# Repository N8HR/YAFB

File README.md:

# Yet Another Foxbox (YAFB)
YAFB is an amateur radio fox transmitter designed for an ESP32-S2-Saola-1 and a NiceRF SA818.

Still being worked on and is not in a functional state but there is a cool logo to look at!

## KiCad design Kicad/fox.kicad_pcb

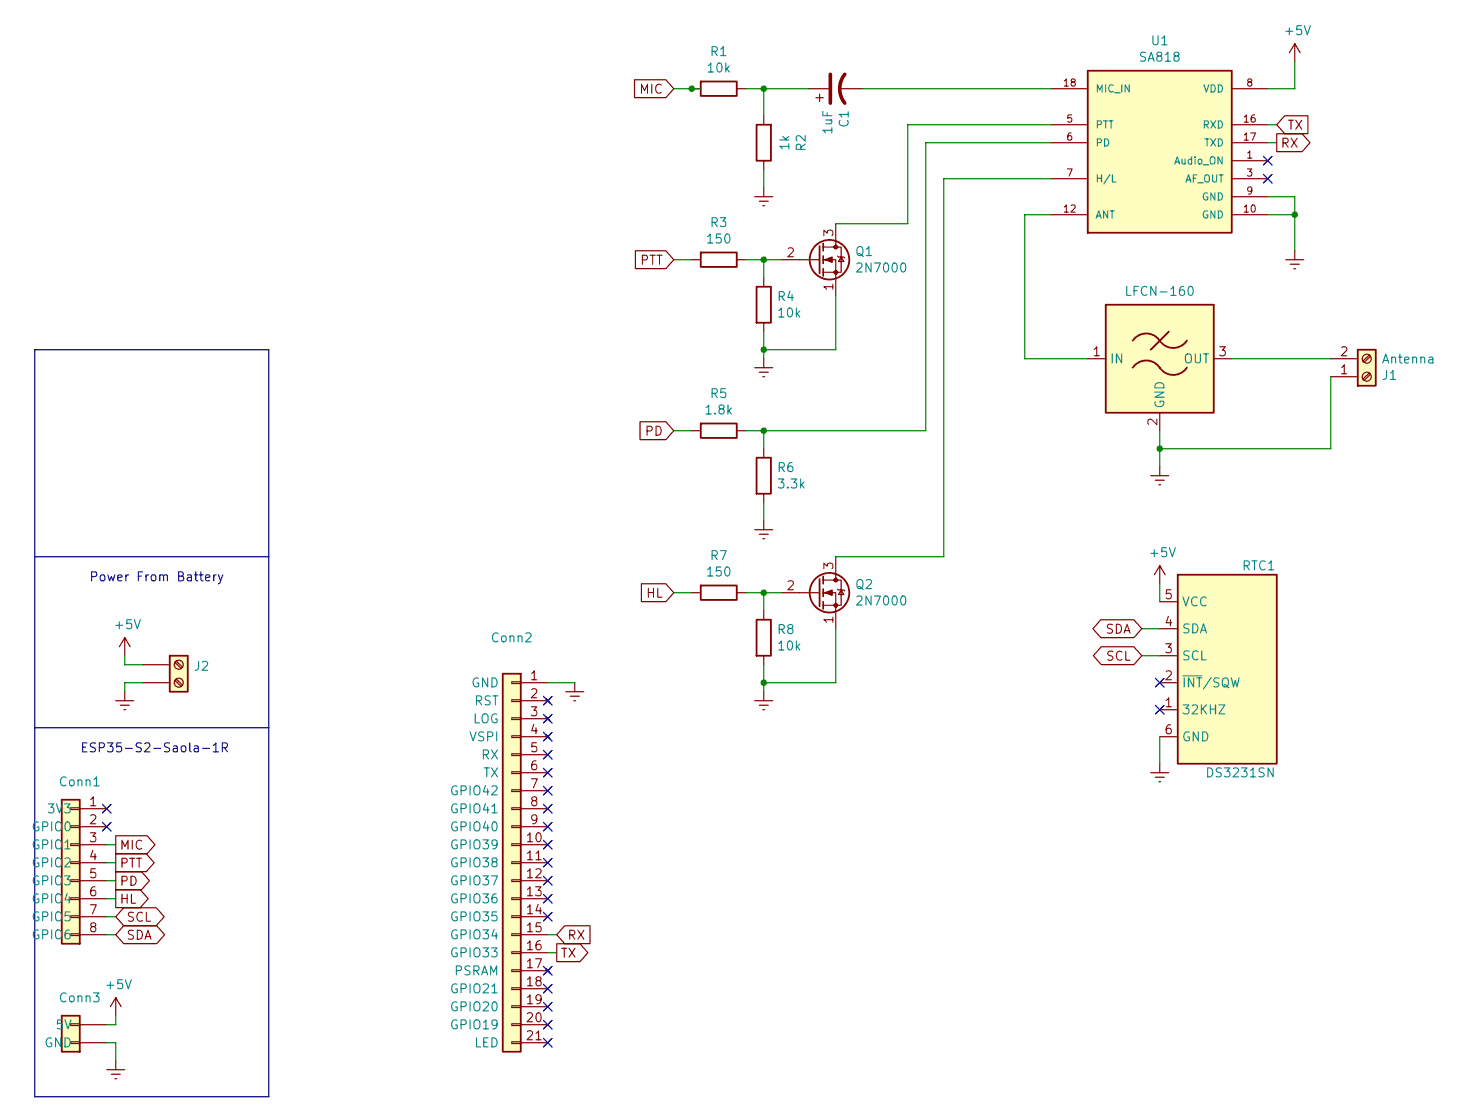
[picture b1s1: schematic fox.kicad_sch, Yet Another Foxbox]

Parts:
C1: 1uF; CP_Radial_D5.0mm_P2.50mm
Conn1: ESP32-S2-Saola-1R_GPIO_1; PinSocket_1x08_P2.54mm_Vertical
Conn2: ESP32-S2-Saola-1R_GPIO_2; PinSocket_1x21_P2.54mm_Vertical
Conn3: ESP32-S2-Saola-1R_Power; PinSocket_1x02_P2.54mm_Vertical
FL1: LFCN-160; Filter_Mini-Circuits_FV1206
J1: Antenna; OSTTA020161
J2: Power; OSTTA020161
Q1, Q2: 2N7000; TO-92_Inline_Wide
R1, R4, R8: 10k; R_Axial_DIN0207_L6.3mm_D2.5mm_P7.62mm_Horizontal
R2: 1k; R_Axial_DIN0207_L6.3mm_D2.5mm_P7.62mm_Horizontal
R3, R7: 150; R_Axial_DIN0207_L6.3mm_D2.5mm_P7.62mm_Horizontal
R5: 1.8k; R_Axial_DIN0207_L6.3mm_D2.5mm_P7.62mm_Horizontal
R6: 3.3k; R_Axial_DIN0207_L6.3mm_D2.5mm_P7.62mm_Horizontal
RTC1: DS3231SN
U1: SA818; DRA818; PART_REV 1.23

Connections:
+5V: Conn3.5v0 (5V), J2.1, RTC1.5 (VCC), U1.8 (VDD)
GNDREF: Conn2.1 (GND), Conn3.GND, FL1.2 (GND), FL1.4 (GND), J1.1, J2.2, Q1.1 (S), Q2.1 (S), R2.1, R4.2, R6.2, R8.2, RTC1.6 (GND), U1.9 (GND), U1.10 (GND)
HL: Conn1.6 (GPIO4), R7.2
MIC: Conn1.3 (GPIO1), R1.2
unnamed: C1.1, R1.1, R2.2
unnamed: C1.2, U1.18 (MIC_IN)
unnamed: FL1.1 (IN), U1.12 (ANT)
unnamed: FL1.3 (OUT), J1.2
unnamed: Q1.2 (G), R3.1, R4.1
unnamed: Q1.3 (D), U1.5 (PTT)
unnamed: Q2.2 (G), R7.1, R8.1
unnamed: Q2.3 (D), U1.7 (H/L)
unnamed: R5.1, R6.1, U1.6 (PD)
PD: Conn1.5 (GPIO3), R5.2
PTT: Conn1.4 (GPIO2), R3.2
RX: Conn2.15 (GPIO34), U1.17 (TXD)
SCL: Conn1.7 (GPIO5), RTC1.3 (SCL)
SDA: Conn1.8 (GPIO6), RTC1.4 (SDA)
TX: Conn2.16 (GPIO33), U1.16 (RXD)

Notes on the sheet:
ESP35-S2-Saola-1R
Power From Battery

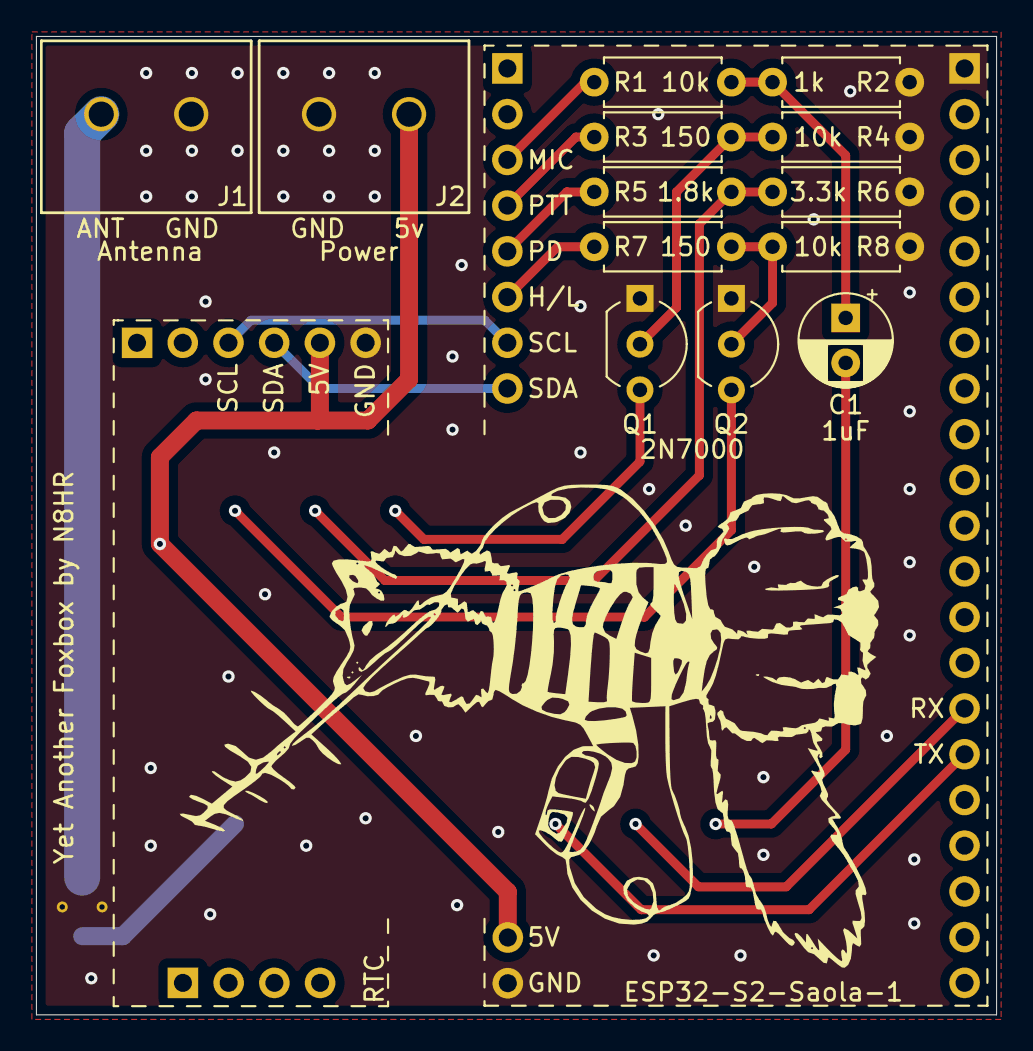
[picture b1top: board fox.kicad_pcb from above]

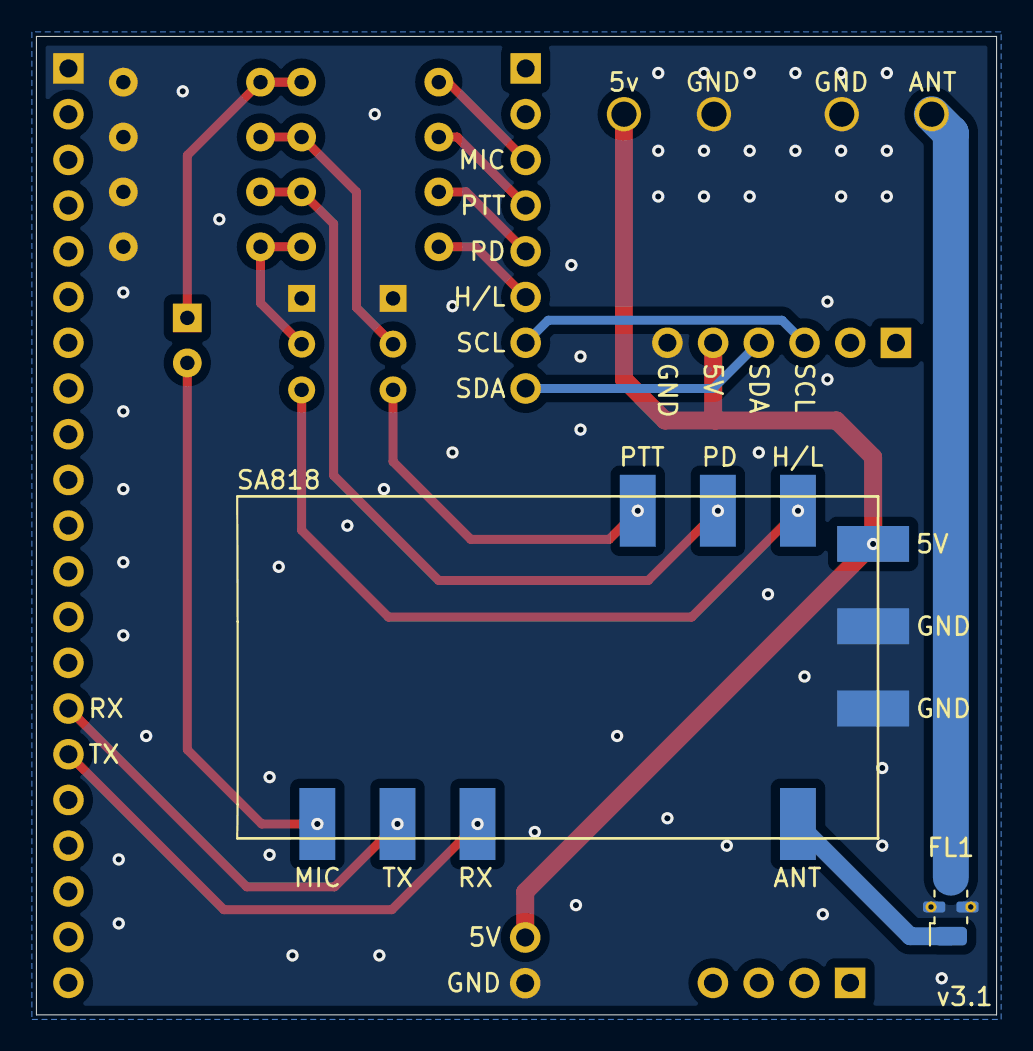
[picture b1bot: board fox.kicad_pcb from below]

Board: 2 copper layers, 53.3 x 54.4 mm, 19 parts (2 on the bottom side), 19 nets.

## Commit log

2021-02-02 Trying to figure out hot to set time/date
2021-02-25 added #include "soc/rtc_io_reg.h" to fix compile error
2021-02-25 added #include "soc/rtc_io_reg.h" to fix complie errors
2021-02-25 in onTimer() changed DacPin from 25,26 (esp32) to 17,18 (esp32-s2)
2021-02-25 changed TEMPLATE_PLACEHOLDER '~' instead of '%' to prevent conflict with css. ex: width: 100%
2021-03-12 Create LICENSE
2023-03-05 Add files via upload
    v3 of the PCB
2023-03-25 Added v3.1
2023-03-25 v3.1
2023-03-25 Made it prettier
2023-03-25 Changed from old callsign to new callsign
2023-03-25 Added Rough Draft of Parts Section
2023-03-25 Create LICENSE - Hardware
2023-03-25 Rename LICENSE to LICENSE - Software
2023-03-25 Added Licenses Section
2023-03-25 Changed license from GPL-3.0-only to GPL-3.0-or-later
2023-09-06 Changed GPL Header
2023-09-06 Updated and removed items for transition to v4
2023-09-06 Changed from WiFi to Bluetooth
2024-04-23 Revert "Add files via upload"
    This reverts commit d908514508931cefb2d773a01c08cfbc2e362328.
2024-04-23 Update README.md
    fix image alignment
2025-11-24 Update README.md
    Admit

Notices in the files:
parts and their libraries:
Copyright 2016 Accelerated Designs. All rights reserved.
